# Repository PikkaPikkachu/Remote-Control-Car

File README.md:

# Remote Control Car with Arduino 

## Introduction
This repository contains various arduino projects that were carried under "Indo-Spanish" project — a collaboration of Indian student from NSIT (under Dr. Pinaki Chakraborty) with Spanish Students from URJC university (under Dr. Cristina Rodriguez).

## Projects

- Introduction to Arduino : This was a brief introduction of Arduino and its working. 

- Traffic Light Signalling

- Air Conditioning

- Final Assessment: Remote Control Car :
For our final project, we built a remote control car simulation, the Spanish members implemented the same in hardware. The simulation can be found [here](https://www.tinkercad.com/things/i8wXkNHVHZt). 

## Car Design

The remote control car makes use of IR sensor and IR remote for sending and receiving signals. The design provides the following functionality: 

1. Move forward/Backward
2. Stop/Turn
3. Turn headlights on/off
4. Automatically turn LED on to signal stop 

Working on: 

1. Adding fan to prevent the car from heating up
2. Automatically turn headlights on during the night time

## Simulate
The simulation on TinkerCad can be found [here](https://www.tinkercad.com/things/i8wXkNHVHZt)."Fork" this simulation to your TinkerCad and start tinkering!  

## Feedback?
Our car design is open to suggestions/feedback. Open an issue and tell us what you think about our design !

## License 
[Apache License 2.0](https://github.com/PikkaPikkachu/Remote-Control-Car/blob/master/LICENSE)

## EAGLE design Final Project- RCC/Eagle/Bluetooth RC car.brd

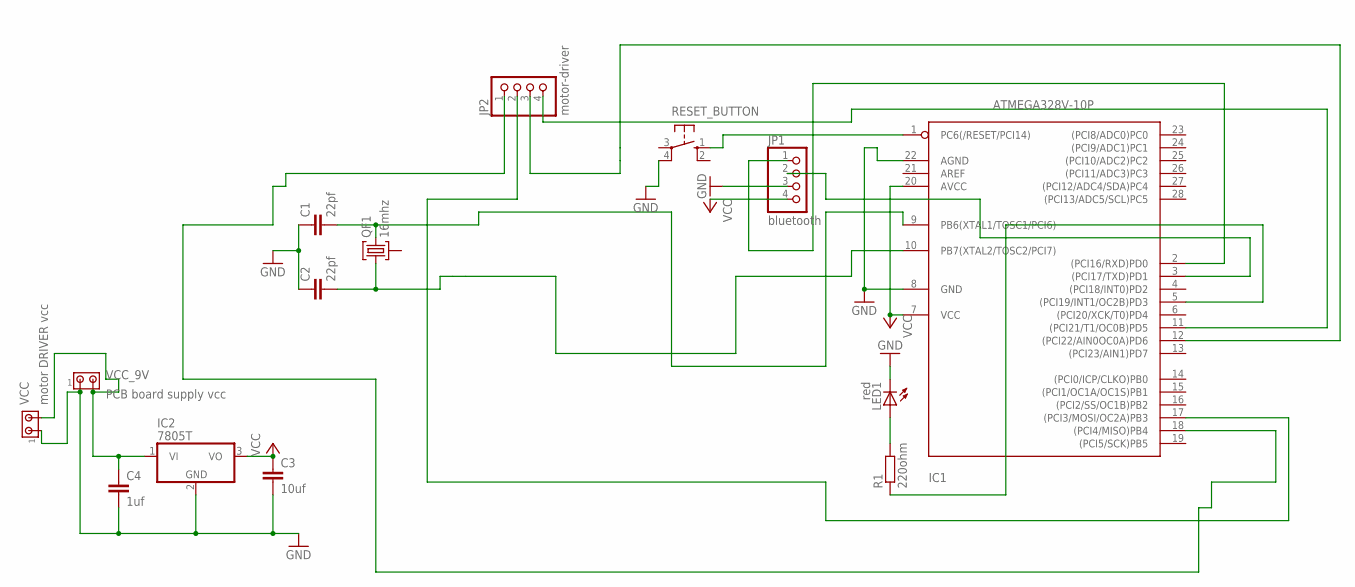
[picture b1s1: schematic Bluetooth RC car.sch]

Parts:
C1, C2: 22pf; C5B2.5
C3: 10uf; C5B3
C4: 1uf; C5B3
IC1: ATMEGA328V-10P; DIL28-3
IC2: 7805T; TO220H
JP1: bluetooth; 1X04
JP2: motor-driver; 1X04
LED1: red; LED5MM
QF1: 16mhz; UM1
R1: 220ohm; 0207/7
RESET_BUTTON: 40-XX; B3F-40XX
VCC: motor DRIVER vcc; 10X02MTA
VCC_9V: PCB board supply vcc; 10X02MTA

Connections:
GND: C1.1, C2.1, C3.2, C4.2, IC1.8 (GND), IC1.22 (AGND), IC2.2 (GND), JP1.3, LED1.K (C), RESET_BUTTON.4 (P1), VCC.1, VCC_9V.1
unnamed: IC1.1 (PC6(/RESET/PCI14)), RESET_BUTTON.1 (S)
unnamed: C4.1, IC2.1 (VI), VCC.2, VCC_9V.2
unnamed: IC1.5 ((PCI19/INT1/OC2B)PD3), R1.1
unnamed: LED1.A, R1.2
unnamed: IC1.2 ((PCI16/RXD)PD0), JP1.1
unnamed: IC1.11 ((PCI21/T1/OC0B)PD5), JP2.4
unnamed: IC1.18 ((PCI4/MISO)PB4), JP2.1
unnamed: IC1.3 ((PCI17/TXD)PD1), JP1.2
unnamed: IC1.17 ((PCI3/MOSI/OC2A)PB3), JP2.2
unnamed: IC1.12 ((PCI22/AIN0OC0A)PD6), JP2.3
unnamed: C1.2, IC1.9 (PB6(XTAL1/TOSC1/PCI6)), QF1.3
unnamed: C2.2, IC1.10 (PB7(XTAL2/TOSC2/PCI7)), QF1.1
VCC: C3.1, IC1.7 (VCC), IC1.20 (AVCC), IC2.3 (VO), JP1.4

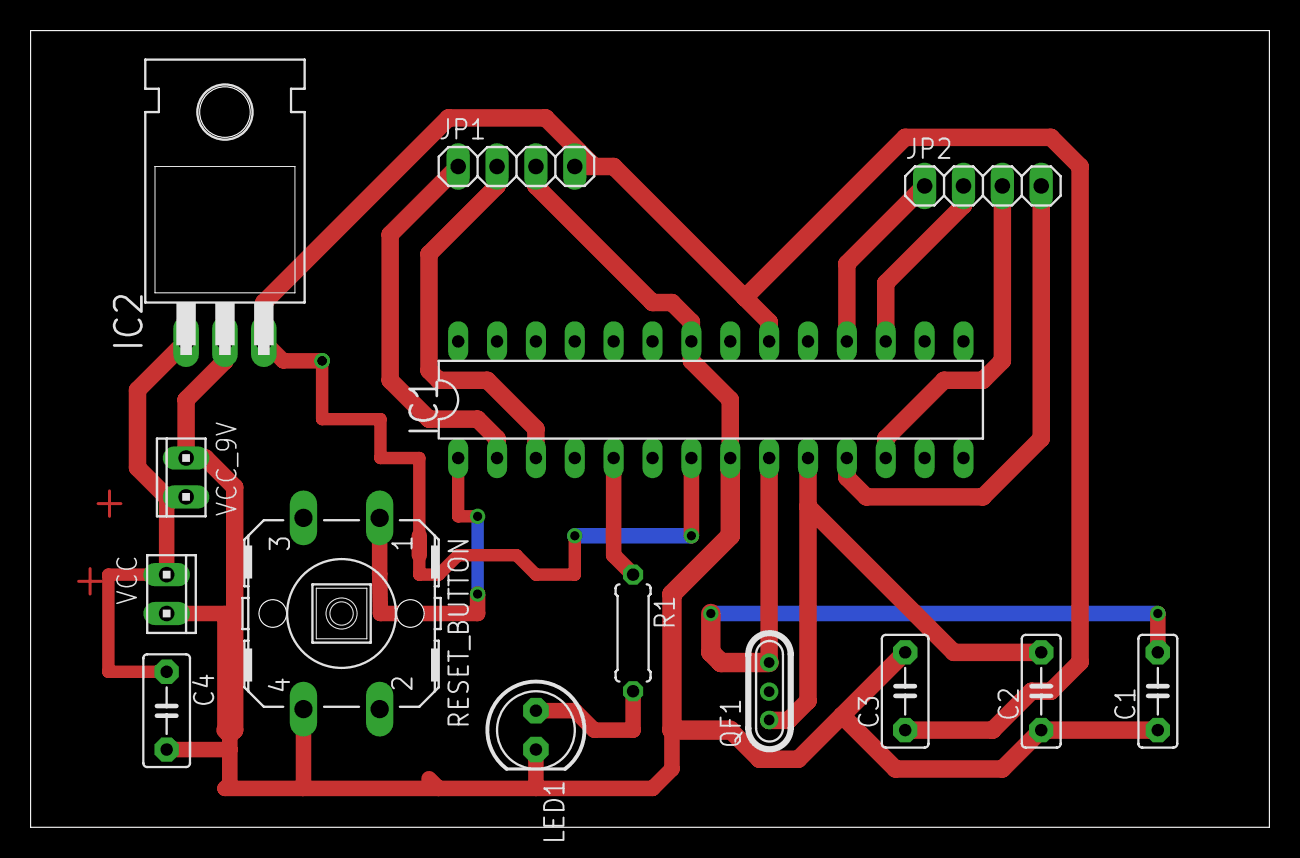
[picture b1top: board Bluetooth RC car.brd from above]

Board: 2 copper layers, 81.0 x 52.1 mm, 14 parts (0 on the bottom side), 14 nets.
